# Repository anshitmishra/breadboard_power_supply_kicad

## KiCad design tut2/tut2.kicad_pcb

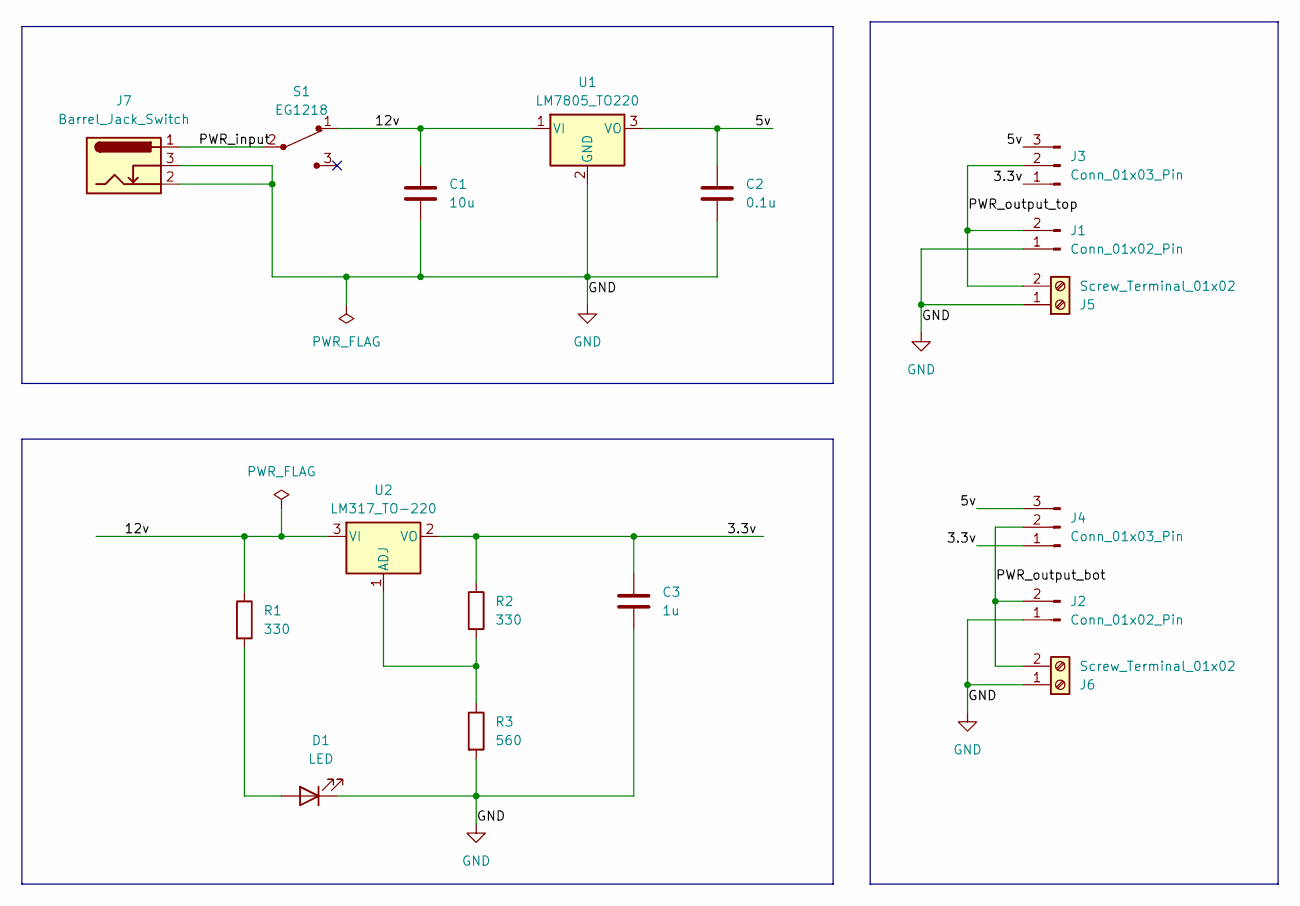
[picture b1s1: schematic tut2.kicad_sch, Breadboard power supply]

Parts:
C1: 10u; C_Disc_D3.0mm_W1.6mm_P2.50mm
C2: 0.1u; C_Disc_D3.0mm_W1.6mm_P2.50mm
C3: 1u; C_Disc_D3.0mm_W1.6mm_P2.50mm
D1: LED; LED_D3.0mm
J1, J2: Conn_01x02_Pin; PinHeader_1x02_P1.27mm_Vertical
J3, J4: Conn_01x03_Pin; PinHeader_1x03_P1.27mm_Vertical
J5, J6: Screw_Terminal_01x02; TerminalBlock_bornier-2_P5.08mm
J7: Barrel_Jack_Switch; BarrelJack_GCT_DCJ200-10-A_Horizontal
R1, R2: 330; R_Axial_DIN0204_L3.6mm_D1.6mm_P7.62mm_Horizontal
R3: 560; R_Axial_DIN0204_L3.6mm_D1.6mm_P7.62mm_Horizontal
S1: EG1218; Switch_Slide_11.6x4mm_EG1218; MPN EG1218; Digi-Key_PN EG1903-ND
U1: LM7805_TO220; TO-220-3_Vertical
U2: LM317_TO-220; TO-220-3_Vertical

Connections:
/3.3v: C3.1, J3.1, J4.1, R2.1, U2.2 (VO)
/5v: C2.1, J3.3, J4.3, U1.3 (VO)
/12v: C1.1, R1.1, S1.1, U1.1 (VI), U2.3 (VI)
/PWR_input: J7.1, S1.2
/PWR_output_bot: J2.2, J4.2, J6.2
/PWR_output_top: J1.2, J3.2, J5.2
GND: C1.2, C2.2, C3.2, D1.1 (K), J1.1, J2.1, J5.1, J6.1, J7.2, J7.3, R3.2, U1.2 (GND)
unnamed: D1.2 (A), R1.2
unnamed: R2.2, R3.1, U2.1 (ADJ)

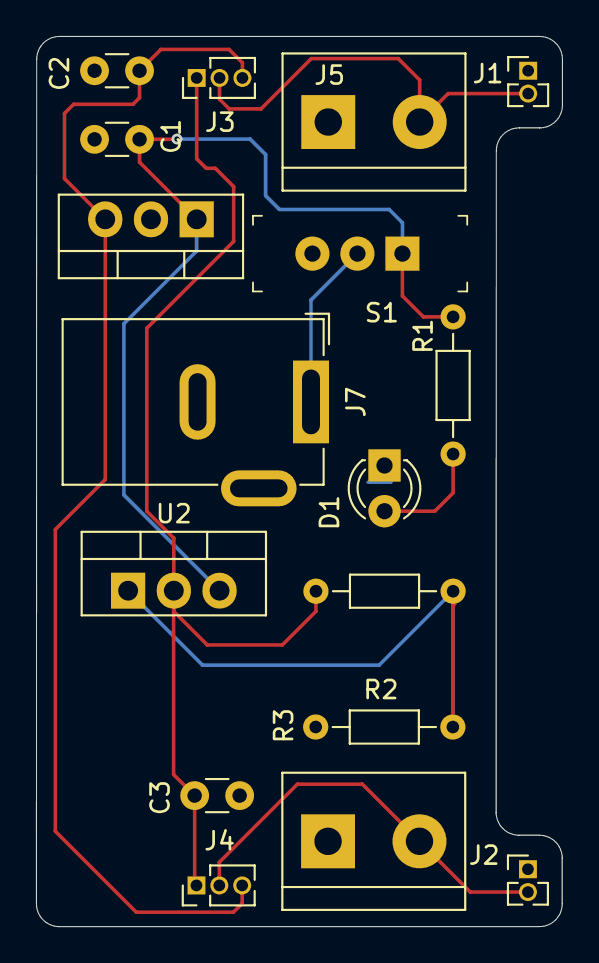
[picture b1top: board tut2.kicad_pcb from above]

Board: 2 copper layers, 29.2 x 49.5 mm, 17 parts (0 on the bottom side), 9 nets.

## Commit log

2025-10-19 init
